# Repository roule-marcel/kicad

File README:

Installation:
=============
ubuntu 15.04:
-------------
sudo add-apt-repository --yes ppa:js-reynaud/kicad-4
sudo apt-get update
sudo apt-get install kicad
sudo apt-get install xsltproc # CSV BOM generation

Configuration:
==============
Pcbnew lib path:
----------------
Open Pcbnew
Preferences > Configure Paths
Add a variable named MARCEL which points to your working dir

Tuto:
=====

General tutorial:
-----------------
http://docs.kicad-pcb.org/en/getting_started_in_kicad.html

Add a logo on the PCB
---------------------
http://www.re-innovation.co.uk/web12/index.php/en/blog-75/230-adding-logo-to-kicad

Generates gerber files for http://dirtypcbs.com/
------------------------------------------------
File > Plot
In the "Layers" pannel, check the following boxes:
F.Cu (Top Copper)
B.Cu (Bottom Copper)
F.SilkS (Top Silkscreen)
B.SilkS (Bottom Silkscreen)
F.Mask (Top Soldermask)
B.Mask (Bottom Soldermask)
Edge.Cuts (Board Outline)

Check "Use Protel filename extensions"
Click "Plot"
The extension of the Edge.Cuts file is ".gm1", change it to ".gml" (change "one" to "L"). 

Click "Generate Drill File"
Put "Drill Units" in "Millimeters", we're civilized here
Click "Drill File"
dirtypcbs wants drill file to be a .txt, please rename it

Known Issues:
=============
You get errors while importing the netlist in Pcbnew?
 -> Re-generate Netlist in Eeschema
 -> Should be done after component-footprint association with Cvpcb

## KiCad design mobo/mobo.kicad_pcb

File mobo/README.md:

#Marcel Motherboard
Au vu du [schéma](http://www.myirtech.com/download/Zynq7000/Z-TURN_SCH_V4_20150326.pdf) (chercher VDD_5V en page 14), on peut alimenter la carte en 5V par les GPIO CN1 et CN2. 
De cette manière seul le fusible (2A) est shunté.

##Alim 5V
Solution 3A la moins chère chez RS :
* SWITCHING REGULATOR 3A [NCP3170B](http://fr.rs-online.com/web/p/convertisseurs-buck/8024293/)
* [Documentation](https://www.onsemi.com/pub/Collateral/NCP3170-D.PDF)
* [Inductance](http://fr.rs-online.com/web/p/inductances-cms-bobinees/8135674/)
* [Condensateur](http://fr.rs-online.com/web/p/condensateurs-ceramique-multicouche/4646701/)

##Pont en H
Moins cher que L6205PD ?
* ON-semi, mais beaucoup de composants autour et un peu moins de courant
* L298, pareil + les diodes de roues-libre à ajouter
* L6205 dans un autre boitier
* Infineon TLE 5206-2G boitier PG-TO263-7-1, 1 seul pont, mais 2x moins cher (même prix donc).
Cela dit, super simpliste, juste besoin d'ajouter la capa de découplage (100uF//100nF).
Et pour le même prix, plus de courant!
[Lien RS](http://fr.rs-online.com/web/p/drivers-de-moteur/9064337/)
[Datasheet](http://docs-europe.electrocomponents.com/webdocs/1478/0900766b81478143.pdf)

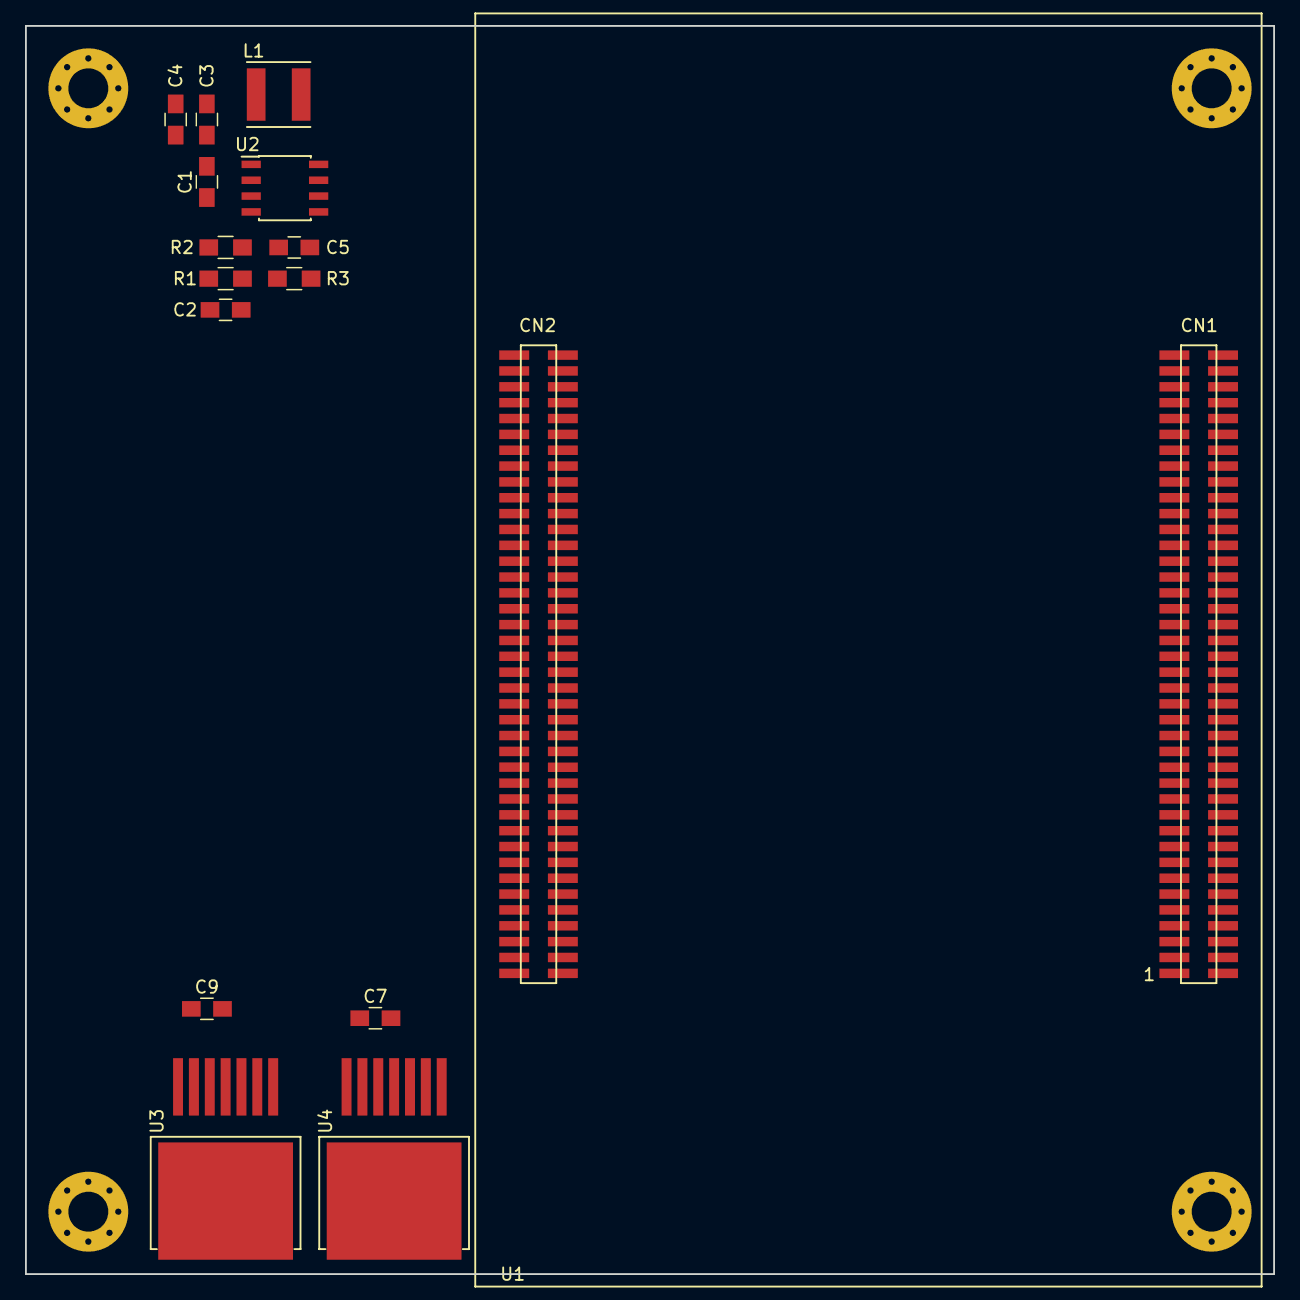
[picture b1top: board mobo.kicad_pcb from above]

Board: 2 copper layers, 100.0 x 100.0 mm, 15 parts (0 on the bottom side), 9 nets, no tracks yet.

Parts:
C1, C3, C4: 22nF; C_0805_HandSoldering
C2: 82pF; C_0805_HandSoldering
C5: 2.2nF; C_0805_HandSoldering
C7, C9: 100nF; C_0805_HandSoldering
L1: 4.7uH; Inductor_Taiyo-Yuden_MD-5050
R1: 24.9k; R_0805_HandSoldering
R2: 4.75k; R_0805_HandSoldering
R3: 8.25k; R_0805_HandSoldering
U1: Z-turn
U2: ncp3170; SOIC-8_3.9x4.9mm_Pitch1.27mm
U3, U4: TLE5206-2G; PG-TO263-7-1

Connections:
+3V3: U1.3, U1.83
+5VD: C2.1, C3.1, C4.1, L1.2, R1.1, U1.1, U1.81
+BATT: C1.1, C7.1, C9.1, U2.2, U2.6, U3.6, U4.6
GNDD: C1.2, C5.2, C7.2, C9.2, R2.2, U1.2, U1.4, U1.24, U1.25, U1.34, U1.35, U1.44, U1.54, U1.67, U1.68, U1.82, U1.84, U1.90, U1.100, U1.101, U1.110, U1.111, U1.120, U1.121, U1.130, U1.140, U1.141, U1.150, U1.151, U1.160, U2.1, U2.3, U3.4, U4.4
unnamed: C2.2, R1.2, R2.1, U2.4
unnamed: C3.2, C4.2
unnamed: C5.1, R3.2
unnamed: L1.1, U2.8
unnamed: R3.1, U2.5

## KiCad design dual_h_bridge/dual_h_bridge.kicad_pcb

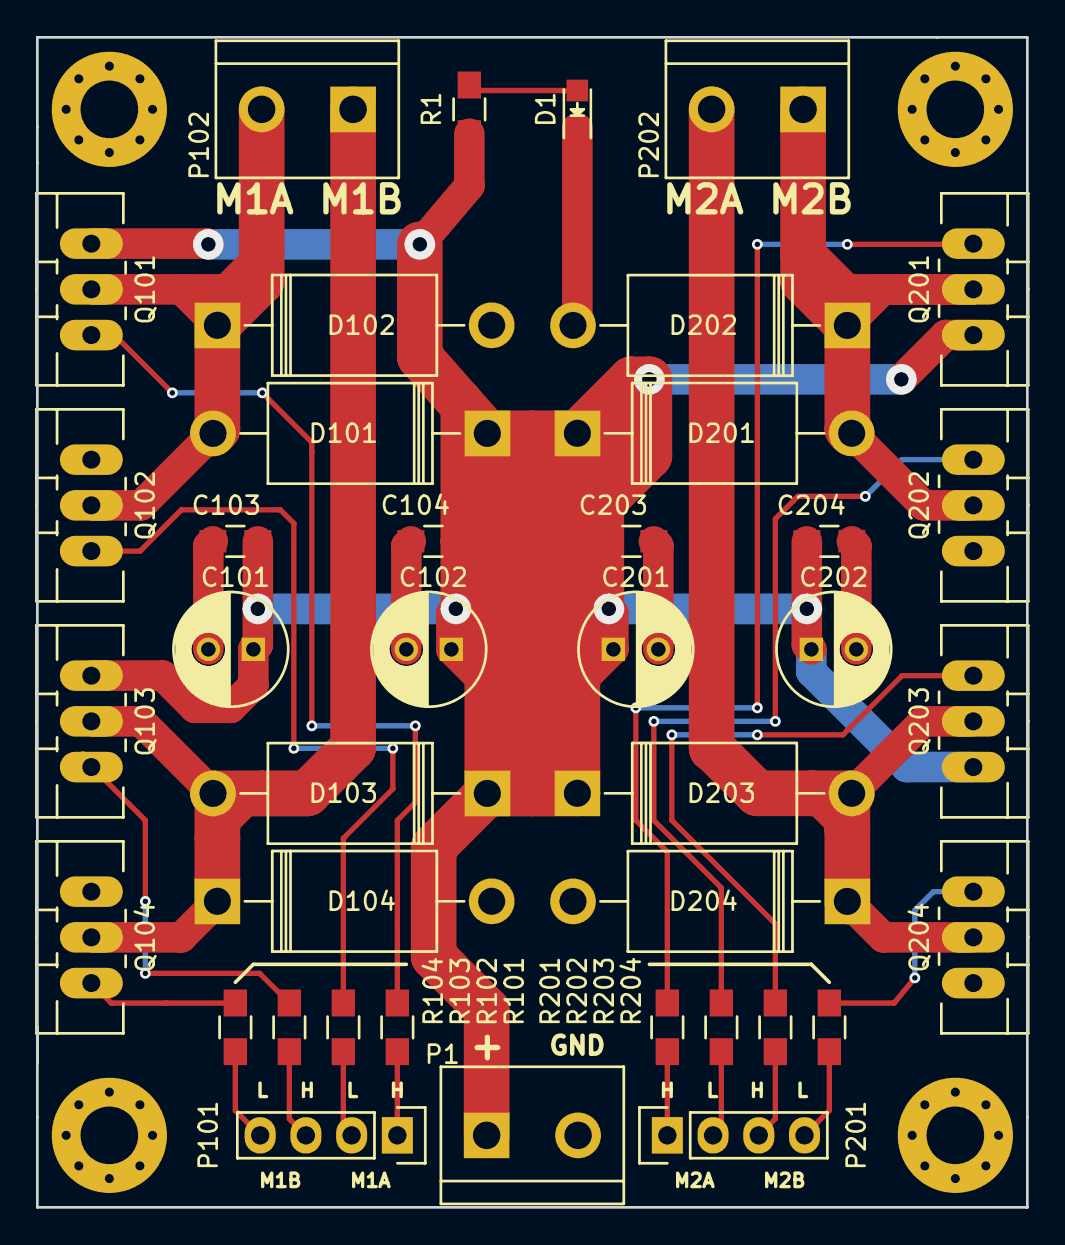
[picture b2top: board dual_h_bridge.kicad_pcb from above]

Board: 2 copper layers, 55.0 x 65.0 mm, 39 parts (0 on the bottom side), 23 nets.

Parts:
C101, C102, C201, C202: CP; C_Radial_D6.3_L11.2_P2.5
C103, C104, C203, C204: C; C_0805_HandSoldering
D1: LED; LED_0805
D101, D102, D103, D104, D201, D202, D203, D204: D; Diode_DO-201AD_Horizontal_RM15
P1, P102, P202: CONN_01X02; bornier2
P101, P201: CONN_01X04; Pin_Header_Straight_1x04
Q101, Q103, Q201, Q203: Q_PNP_BCE; TO-220_Neutral123_Vertical_LargePads
Q102, Q104, Q202, Q204: Q_NPN_BCE; TO-220_Neutral123_Vertical_LargePads
R1: 1k; R_0805_HandSoldering
R101, R102, R103, R104, R201, R202, R203, R204: 10k; R_0805_HandSoldering

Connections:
+BATT: C101.1, C102.1, C103.1, C104.1, C201.1, C202.1, C203.1, C204.1, D101.1, D103.1, D201.1, D203.1, P1.1, Q101.3, Q103.3, Q201.3, Q203.3, R1.1
GND: C101.2, C102.2, C103.2, C104.2, C201.2, C202.2, C203.2, C204.2, D1.1, D102.2, D104.2, D202.2, D204.2, P1.2, Q102.3, Q104.3, Q202.3, Q204.3
M1A: D101.2, D102.1, P102.2, Q101.2, Q102.2
M1A_H: P101.1, R101.2
M1A_L: P101.2, R102.2
M1B: D103.2, D104.1, P102.1, Q103.2, Q104.2
M1B_H: P101.3, R103.1
M1B_L: P101.4, R104.1
M2A: D201.2, D202.1, P202.1, Q201.2, Q202.2
M2A_H: P201.1, R201.2
M2A_L: P201.2, R202.2
M2B: D203.2, D204.1, P202.2, Q203.2, Q204.2
M2B_H: P201.3, R203.1
M2B_L: P201.4, R204.1
unnamed: D1.2, R1.2
unnamed: Q101.1, R101.1
unnamed: Q102.1, R102.1
unnamed: Q103.1, R103.2
unnamed: Q104.1, R104.2
unnamed: Q201.1, R201.1
unnamed: Q202.1, R202.1
unnamed: Q203.1, R203.2
unnamed: Q204.1, R204.2

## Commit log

2016-04-26 Added a board to test Bi-polar based H-Bridge
2016-04-26 Completed BOM for the Dual H-Bridge
2016-04-28 Completed BOM on Dual H-Bridge
2016-05-10 List of TODOs for the Dual H-Bridge
2017-02-24 mobo: z-turn schematic library
2017-02-24 added pinout documentation
2017-02-27 mobo: z-turn footprint library
2017-02-27 some doc for later
2017-02-28 calculs alim 5V
2017-03-01 5V Power supply schematic + place
2017-03-01 started h-bridge
